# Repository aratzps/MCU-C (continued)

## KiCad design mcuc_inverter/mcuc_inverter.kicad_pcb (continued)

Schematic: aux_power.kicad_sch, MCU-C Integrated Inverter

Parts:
C601, C602: 0.68uF 630VDC X2 film; C_Rect_L26.5mm_W10.5mm_P22.50mm_MKS4; Rating Radial box 26.5 x 16.5 x 10.5 mm, 22.5 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
C603: 6.8nF 630V C0G; C_1210_3225Metric; Rating TDK CGA5H4C0G2J682J115AE (DER-948Q clam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
C604, C640, C645: 10uF 50V X7R; C_1210_3225Metric
C606: 0.47uF 50V X7R; C_0805_2012Metric; Rating BPP: 0.47uF selects STANDARD ILIMIT (CR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
C607: 100nF 50V X7R; C_0805_2012Metric
C608: 1nF 200V C0G; C_0805_2012Metric
C609, C610: 220uF 25V polymer [TBV]; CP_Elec_8x10.5
C611, C622, C623, C642, C646, C661, C663, C665, C667, C669, C671, C673, C675, C677, C679, C681, C683: 100nF; C_0603_1608Metric
C612: 270pF; C_0603_1608Metric
C613, C625: 10nF [TBV]; C_0603_1608Metric
C614: 2.2uF 25V X7R; C_0805_2012Metric; Rating BPS: 0805 min per datasheet (>=1.5uF in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
C620, C621: 4.7uF 50V [TBV]; C_0805_2012Metric
C624: 4.7uF [TBV]; C_0603_1608Metric
C626: 100pF [TBV]; C_0603_1608Metric
C627: 47nF [TBV]; C_0603_1608Metric
C628: 130pF; C_0603_1608Metric
C629, C630, C643, C644, C647, C648: 22uF 25V [TBV]; C_1210_3225Metric
C631: 1uF [TBV]; C_0603_1608Metric
C641, C649: 220nF 50V X7R; C_0603_1608Metric
C650, C651, C653, C660, C666, C672, C678: 10uF [TBV]; C_0805_2012Metric
C652: 2.2uF [TBV]; C_0603_1608Metric
C654, C655: 1uF 16V X7R; C_0603_1608Metric
C662, C664, C668, C670, C674, C676, C680, C682: 10uF 25V [TBV]; C_0805_2012Metric
C684, C685, C686, C687: 10uF 25V X7R; C_0805_2012Metric
D601: US1M-class 1kV std recovery [TBV]; D_SMA
D602: BAS316-class [TBV]; D_SOD-323
D603: SS310-class 100V 3A [TBV]; D_SMC
D604: SS54 [TBV]; D_SMC
D605, D606, D608, D609, D611, D612, D614, D615: SS310 [TBV]; D_SMC
D607, D610, D613, D616: MM3Z4V7ST1G 4.7V; D_SOD-323
D620: BZX384-C9V1 [TBV]; D_SOD-323
D621, D622, D623, D624: MMSZ5245C-E3-08 15V 2%; D_SOD-123
D625, D626, D627, D628: 1N4148W-7-F; D_SOD-123
D629: SMCJ36CA; D_SMC
D630: MMSZ5243BT1G 13V; D_SOD-123
L601, L602: SRP6060FA-100M 10uH 7.6A; L_Bourns_SRP6060FA
L603: SRR1260-120M 12uH 5A; L_Bourns_SRR1260
Q601, Q602, Q603, Q604, Q605: CSD18543Q3A-class [TBV]; VSON-8_3.3x3.3mm_P0.65mm_NexFET
Q606, Q607, Q608, Q609: BCP56-16T1G; SOT-223-3_TabPin2
Q610: DMP6023LE-13; SOT-223-3_TabPin2
R603, R604, R612, R613, R614, R615: 39k; R_1206_3216Metric; Rating 0.5W 200V working (ROHM ESR18EZPJ393); Tolerance 5%
R605: 4.7R; R_1206_3216Metric; Rating 0.5W 200V working (ROHM ESR18EZPJ4R7)
R606: 8.2k [TBV]; R_0603_1608Metric
R607: 100R [TBV]; R_0603_1608Metric
R608: 10R; R_1206_3216Metric; Rating 0.5W 200V working (ROHM ESR18EZPJ100); 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
R609: 143k 1%; R_0603_1608Metric
R610: 13.2k 1%; R_0603_1608Metric
R611: 10k [TBV]; R_0603_1608Metric
R616, R617, R618, R619: 300k; R_1206_3216Metric; Tolerance 1%; Rating 0.5W 200V working (ROHM ESR18 class)
R620: 100k [TBV]; R_0603_1608Metric
R621: 16.2k [TBV]; R_0603_1608Metric
R622: 30mR 1%; R_2512_6332Metric
R623: 97.6k 1%; R_0603_1608Metric
R624: 4.99k 1%; R_0603_1608Metric
R625: 24.9k [TBV]; R_0603_1608Metric
R626: 84.5k (300kHz) [TBV]; R_0603_1608Metric
R627: 93.1k (CCM+hiccup) [TBV]; R_0603_1608Metric
R630: 210k; R_0603_1608Metric; Tolerance 1%; Rating 0.5W 200V working (ROHM ESR18EZPJ4R7)
R640, R642: 100k 1%; R_0603_1608Metric
R641: 24.9k 1%; R_0603_1608Metric
R643: 9.09k 1%; R_0603_1608Metric
R644, R645, R646, R647: 470R 1%; R_0603_1608Metric
R648: 100k; R_0603_1608Metric
T601: custom flyback per DER-948Q T1: Lp 422.6uH, 25T:2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; T_FLYBACK_EQ30
T602, T603, T604, T605: 750316856; WE_PPTI_750316856
U601: INN3990CQ; InSOP-24D
U603: LM5175RHFR; VQFN-28-1EP_4x5mm_P0.5mm_EP2.55x3.55mm
U604: LM74610QDGKRQ1; VSSOP-8_3x3mm_P0.65mm
U605, U606: LMR33630ADDAR; SOIC-8-1EP_3.9x4.9mm_P1.27mm_EP2.95x4.9mm_Mask2.71x3.4mm
U607: TLV1117-33; SOT-223-3_TabPin2
U608: NXE2S0505MC; Converter_DCDC_Murata_NXExSxxxxMC_SMD
U609, U610, U611, U612: SN6505BDBVR; SOT-23-6

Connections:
+5V: C643.1, C644.1, C650.1, C652.1, C660.1, C661.1, C666.1, C667.1, C672.1, C673.1, C678.1, C679.1, L602.2, R640.1, T602.2 (CT_PRI), T603.2 (CT_PRI), T604.2 (CT_PRI), T605.2 (CT_PRI), U607.3 (VI), U608.3 (+VIN), U609.2 (VCC), U609.5 (EN), U610.2 (VCC), U610.5 (EN), U611.2 (VCC), U611.5 (EN), U612.2 (VCC), U612.5 (EN); also elsewhere on the board
+12V: C647.1, C648.1, L603.2, R642.1; also elsewhere on the board
/AUX_IN: D629.1 (A1), Q610.2 (D); also elsewhere on the board
/Auxiliary power/AUX_15V: C640.1, C641.1, C645.1, C649.1, D604.1 (K), Q605.5 (D), U604.8 (CATHODE), U605.2 (VIN), U605.3 (EN), U606.2 (VIN), U606.3 (EN)
/Auxiliary power/AUX_IN_P: C620.1, C621.1, D630.1 (K), Q601.5 (D), Q610.3 (S), R620.1, U603.27 (VIN), U603.28 (VISNS)
/Auxiliary power/BB_15V: C629.1, C630.1, Q604.5 (D), Q605.1 (S), Q605.2 (S), Q605.3 (S), R623.1, U603.9 (VOSNS), U603.10 (ISNS(-)), U603.11 (ISNS(+)), U603.21 (BIAS), U604.4 (ANODE)
/Auxiliary power/BB_COMP: C626.1, R625.1, U603.6 (COMP)
/Auxiliary power/BB_CS: Q602.1 (S), Q602.2 (S), Q602.3 (S), Q603.1 (S), Q603.2 (S), Q603.3 (S), R622.1, U603.13 (CS)
/Auxiliary power/BB_FB: R623.2, R624.1, U603.8 (FB)
/Auxiliary power/BB_MODE: R627.1, U603.1 (MODE)
/Auxiliary power/BB_RT: R626.1, U603.3 (RT/SYNC)
/Auxiliary power/BB_SLOPE: C628.1, U603.4 (SLOPE)
/Auxiliary power/BB_SS: C627.1, U603.5 (SS)
/Auxiliary power/BB_SW1: C622.2, L601.1, Q601.1 (S), Q601.2 (S), Q601.3 (S), Q602.5 (D), U603.25 (SW1)
/Auxiliary power/BB_SW2: C623.2, L601.2, Q603.5 (D), Q604.1 (S), Q604.2 (S), Q604.3 (S), U603.15 (SW2)
/Auxiliary power/BB_VCC: C624.1, U603.20 (VCC)
/Auxiliary power/CLAMP_NODE: C603.2, R605.1, R614.2, R615.2
/Auxiliary power/DC_BUS_P: C601.1, C603.1, R603.1, R604.1, R616.1, T601.3 (PRI+); also elsewhere on the board
/Auxiliary power/FB_5V: R640.2, R641.1, U605.5 (FB)
/Auxiliary power/FB_12V: R642.2, R643.1, U606.5 (FB)
/Auxiliary power/FLY_15V: C608.2, C609.1, C610.1, C611.1, D603.1 (K), D604.2 (A), R609.1, R611.1, U601.6 (VOUT)
/Auxiliary power/VGD_HS1_RAW: C662.1, C663.1, D605.1 (K), D606.1 (K), Q606.2 (C), R644.1
/Auxiliary power/VGD_HS2_RAW: C668.1, C669.1, D608.1 (K), D609.1 (K), Q607.2 (C), R645.1
/Auxiliary power/VGD_HS3_RAW: C674.1, C675.1, D611.1 (K), D612.1 (K), Q608.2 (C), R646.1
/Auxiliary power/VGD_LS_RAW: C680.1, C681.1, D614.1 (K), D615.1 (K), Q609.2 (C), R647.1
/Auxiliary power/V_SENSE: R630.1, U601.13 (V)
/Precharge and contactor/DC_BUS_N: C602.2, C604.2, C606.2, C607.2, D620.2 (A), T601.5 (BIAS-), U601.16 (S), U601.17 (S), U601.18 (S), U601.19 (S); also elsewhere on the board
/VGD_HS1_COM: C662.2, C663.2, C664.1, C665.1, C684.2, D607.1 (K), D621.2 (A); also elsewhere on the board
/VGD_HS1_N: C664.2, C665.2, D607.2 (A), T602.5 (CT_SEC); also elsewhere on the board
/VGD_HS1_P: C684.1, Q606.3 (E); also elsewhere on the board
/VGD_HS2_COM: C668.2, C669.2, C670.1, C671.1, C685.2, D610.1 (K), D622.2 (A); also elsewhere on the board
/VGD_HS2_N: C670.2, C671.2, D610.2 (A), T603.5 (CT_SEC); also elsewhere on the board
/VGD_HS2_P: C685.1, Q607.3 (E); also elsewhere on the board
/VGD_HS3_COM: C674.2, C675.2, C676.1, C677.1, C686.2, D613.1 (K), D623.2 (A); also elsewhere on the board
/VGD_HS3_N: C676.2, C677.2, D613.2 (A), T604.5 (CT_SEC); also elsewhere on the board
/VGD_HS3_P: C686.1, Q608.3 (E); also elsewhere on the board
/VGD_LS_COM: C680.2, C681.2, C682.1, C683.1, C687.2, D616.1 (K), D624.2 (A); also elsewhere on the board
/VGD_LS_N: C682.2, C683.2, D616.2 (A), T605.5 (CT_SEC); also elsewhere on the board
/VGD_LS_P: C687.1, Q609.3 (E); also elsewhere on the board
GND: C609.2, C610.2, C611.2, C612.2, C614.2, C620.2, C621.2, C624.2, C625.2, C626.2, C627.2, C628.2, C629.2, C630.2, C640.2, C641.2, C643.2, C644.2, C645.2, C647.2, C648.2, C649.2, C650.2, C651.2, C652.2, C654.2, C655.2, C660.2, C661.2, C666.2, C667.2, C672.2, C673.2, C678.2, C679.2, D629.2 (A2), R610.2, R621.2, R622.2, R624.2, R626.2, R627.2, R641.2, R643.2, R648.2, T601.9 (SEC-), U601.1 (IS), U601.2 (GND), U601.5 (SR), U603.2 (DITH), U603.7 (AGND), U603.12 (CSG), U603.19 (PGND), U603.29 (PowerPAD), U605.1 (PGND), U605.9 (AGND), U606.1 (PGND), U606.9 (AGND), U607.1 (GND), U608.1 (-VIN), U609.4 (GND), U609.6 (CLK), U610.4 (GND), U610.6 (CLK), U611.4 (GND), U611.6 (CLK), U612.4 (GND), U612.6 (CLK); also elsewhere on the board
unnamed: C601.2, C602.1
unnamed: C608.1, R608.2
unnamed: C613.1, R611.2
unnamed: C625.1, R625.2
unnamed: D601.2 (A), T601.1 (PRI-), U601.24 (D)
unnamed: D601.1 (K), R605.2
unnamed: D602.2 (A), T601.6 (BIAS+)
unnamed: C604.1, D602.1 (K), R606.1
unnamed: D603.2 (A), R607.1, R608.1, T601.8 (SEC+)
unnamed: D605.2 (A), T602.6 (N3.A)
unnamed: D606.2 (A), T602.4 (N4.B)
unnamed: D608.2 (A), T603.6 (N3.A)
unnamed: D609.2 (A), T603.4 (N4.B)
unnamed: D611.2 (A), T604.6 (N3.A)
unnamed: D612.2 (A), T604.4 (N4.B)
unnamed: D614.2 (A), T605.6 (N3.A)
unnamed: D615.2 (A), T605.4 (N4.B)
unnamed: D620.1 (K), R619.2, R630.2
unnamed: D621.1 (K), D625.1 (K)
unnamed: D622.1 (K), D626.1 (K)
unnamed: D623.1 (K), D627.1 (K)
unnamed: D624.1 (K), D628.1 (K)
unnamed: D625.2 (A), Q606.1 (B), R644.2
unnamed: D626.2 (A), Q607.1 (B), R645.2
unnamed: D627.2 (A), Q608.1 (B), R646.2
unnamed: D628.2 (A), Q609.1 (B), R647.2
unnamed: D630.2 (A), Q610.1 (G), R648.1
unnamed: Q601.4 (G), U603.24 (HDRV1)
unnamed: Q602.4 (G), U603.22 (LDRV1)
unnamed: Q603.4 (G), U603.18 (LDRV2)
unnamed: Q604.4 (G), U603.16 (HDRV2)
unnamed: Q605.4 (G), U604.2 (GATE_PD), U604.6 (GATE_DRV)
unnamed: R603.2, R604.2, R612.1, R613.1
unnamed: R612.2, R613.2, R614.1, R615.1
unnamed: R616.2, R617.1
unnamed: R617.2, R618.1
unnamed: R618.2, R619.1
unnamed: T602.1 (N1.A), U609.1 (D1)
unnamed: T602.3 (N2.B), U609.3 (D2)
unnamed: T603.1 (N1.A), U610.1 (D1)
unnamed: T603.3 (N2.B), U610.3 (D2)
unnamed: T604.1 (N1.A), U611.1 (D1)
unnamed: T604.3 (N2.B), U611.3 (D2)
unnamed: T605.1 (N1.A), U612.1 (D1)
unnamed: T605.3 (N2.B), U612.3 (D2)
unnamed: C606.1, C607.1, R606.2, U601.14 (BPP)
unnamed: C614.1, U601.4 (BPS)
unnamed: C612.1, C613.2, R609.2, R610.1, U601.3 (FB)
unnamed: R607.2, U601.7 (FWD)
unnamed: C622.1, U603.23 (BOOT1)
unnamed: C623.1, U603.17 (BOOT2)
unnamed: R620.2, R621.1, U603.26 (EN/UVLO)
unnamed: C631.1, U604.7 (VCAPH)
unnamed: C631.2, U604.1 (VCAPL)
unnamed: C642.1, U605.7 (BOOT)
unnamed: C642.2, L602.1, U605.8 (SW)
unnamed: C654.1, U605.6 (VCC)
unnamed: C646.1, U606.7 (BOOT)
unnamed: C646.2, L603.1, U606.8 (SW)
unnamed: C655.1, U606.6 (VCC)

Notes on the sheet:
Auxiliary power
SPEC.md 11.2b - DECISIONS.md D020. HV flyback (INN3990CQ) -> 15 V main rail; LM5175 buck-boost from 12-24 V AUX_IN OR'd in via LM74610 smart diode; LMR51430 bucks -> 5 V / 12 V; TLV1117 -> 3.3 V; 4x SN6505B+750316856 gate supplies; NXE2S0505MC CAN 5 V.
ISOLATION: primary side of T601 floats at HV bus potential (48-450 V, 500 V transient). Spacing per SPEC 10: >=3.2 mm clearance / >=6.4 mm creepage power->control, T601 reinforced >=4 kV. FluxLink feedback is internal to U601 (no optocoupler). Film caps C601/C602 in series so no single part spans t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
SR pin tied to GND: diode-only rectification (datasheet: 'If no SR FET is used connect this pin to GND'). IS tied to GND: no CC regulation. FB divider 143k/13.2k @ 1.265 V ref -> 14.97 V. Feed-forward 10k + 10 nF per Fig 10.
D604 SS54: plain Schottky OR from flyback into AUX_15V. Penalty ~0.4 V / ~0.7 W at 1.7 A. Upgrade: second LM74610+FET stage [TBV]. Flyback is the primary source; the LM5175 aux path carries the board only when the 12-24 V feed is present (15.02 V > 14.97 - 0.4 V).
Primary OVP chain (not fitted - note per datasheet): zener + series R + blocking diode from the rectified bias rail into BPP triggers latching OVP at ISD. Fit if secondary OVP insufficient [TBV].
AUX input: LM5175 4-switch buck-boost, 12-24 V in -> 15.02 V (FB 88.7k/4.99k @ 0.8 V). fsw 300 kHz (RT 84.5k), CCM+hiccup (MODE 93.1k), all loop/support values [TBV]. EN divider 100k/16.2k -> input UVLO ~8.9 V [TBV]. ISNS+/- shorted (CC loop disabled).
Gate-drive supplies (x4): SN6505B push-pull from +5V (SN6505B is 5 V-only, D020) + WE 750316856 (1:4.67 CT:CT) -> 22-25 V raw full-wave rail (VGD_x_RAW). MM3Z4V7ST1G zener from raw(-) sets COM 4.7 V above it, so COM-N = -4.7 V; the +15 V leg is then POST-REGULATED per D026 (see the note at the left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
+5V / +12V / +3.3V / GND are global power rails sourced on this sheet (PWR_FLAG on +5V here; +12V flagged on precharge sheet, +3.3V and GND flagged on MCU sheet - no duplicates).
CAN supply: functional 3 kVDC isolation. CAN_GND is the isolated CAN return - do not tie to GND.
RAW
COM-4.7 V
MJ-14 FIXED - line UV sense fitted (clamped network, InnoSwitch3-AQ datasheet Fig. 15). R616-R619 4x 300k (RU = 1.20 M) + R630 210k (RL) + D620 9.1 V zener at the RL top node. Brown-in V_UV+ = I_UV+ x (RU+RL) + 1.37 V; I_UV+ 22.1/26.1/30.4 uA over temp -> 32.5 / 38.2 / 44.2 V. Max 44.2 V < the 48 V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
CR-4 FIXED - RCD clamp respec. R603/R604/R612-R615 = 6x 39k 1206 (0.5 W, 200 V working, ROHM ESR18 class) wired 3 series x 2 parallel = 58.5 k. Old build was 2x 390k 0603 in parallel (195 k) on parts rated 75 V / 0.1 W - 3-5x over voltage and over power. V_OR = 15.5 V x 12.5 = 194 V. P_leak = 0.5 x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
CR-5 FIXED - core saturation at the current limit. C606 (BPP) 4.7 uF -> 0.47 uF, which selects the STANDARD I_LIMIT instead of I_LIMIT+1. Controller stays INN3990CQ. B_pk = Lp x I_LIM / (Np x Ae) = 422.6 uH x I / (25 x 108 mm^2) = 0.1565 T/A: was 4.7 uF -> I_LIMIT+1 2.576 A typ / 2.886 A worst -> 4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
MJ-19 - aux input priority (D020) now actually implemented by setpoint offset: flyback 14.97 V (R609/R610 143k/13.2k @ 1.265 V) vs LM5175 16.45 V (R623 88.7k -> 97.6k). Worst case: LM5175 min 16.45 x 0.975 = 16.04 V > flyback max 14.97 x 1.03 = 15.42 V, margin 0.62 V - the aux unit always holds the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
INSULATION CAVEAT (D017) - the four gate-drive transformers T602-T605 (WE 750316856) carry SUPPLEMENTARY / FUNCTIONAL insulation only, 600 Vrms working; their 2.5 kV AC figure is a type-test hipot, not a reinforced certification. The REINFORCED barrier on the gate-drive path therefore rests ENTIREL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
HS1 +15 V post-regulator (D026)
HS2 +15 V post-regulator (D026)
HS3 +15 V post-regulator (D026)
LS +15 V post-regulator (D026)
D026 - +15 V GATE RAIL POST-REGULATION. REQUIRED: the raw rail alone breaks the module AMR. Raw secondary = 5 V +-2.5% x 4.67 = 22.77-23.93 V per half, less the SS310 Vf; at light load the leakage peak-charges the reservoir to ~24.9 V. Minus the COM zener that is V_GS(on) = 20.3 V against the FS02M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
MN-14 FIXED - AUX INPUT PROTECTION (12-24 V feed, J1203 on the comms sheet). Previously a reversed connection ran straight through the LM5175 body diodes with nothing in the way. D629 SMCJ36CA - BIDIRECTIONAL TVS, DO-214AB. Littelfuse SMCJ datasheet: V_RWM 36 V, V_C 58.1 V at rated I_PP at I_T 1 mA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

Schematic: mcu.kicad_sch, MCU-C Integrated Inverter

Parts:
C1, C2, C3, C4, C5, C6, C9, C12: 100nF; C_0603_1608Metric
C7: 4.7uF; C_0805_2012Metric
C8: 1uF; C_0603_1608Metric
C10, C11: 2.2uF; C_0805_2012Metric
C13, C14: 18pF; C_0603_1608Metric
FB1: FerriteBead; L_0805_2012Metric
R1: 10k; R_0603_1608Metric
U1: STM32F405VGT6; LQFP-100_14x14mm_P0.5mm
Y1: 8MHz; Crystal_SMD_5032-2Pin_5.0x3.2mm

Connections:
/CAN1_RX: U1.95 (PB8); also elsewhere on the board
/CAN1_TX: U1.96 (PB9); also elsewhere on the board
/CONTACTOR_EN: U1.2 (PE3); also elsewhere on the board
/DISCHARGE_EN: U1.3 (PE4); also elsewhere on the board
/DRV_RST_IN: U1.86 (PD5); also elsewhere on the board
/ENC_A: U1.63 (PC6); also elsewhere on the board
/ENC_B: U1.64 (PC7); also elsewhere on the board
/ENC_I: U1.65 (PC8); also elsewhere on the board
/FAULT_RESET: U1.85 (PD4); also elsewhere on the board
/HALL_1: U1.59 (PD12); also elsewhere on the board
/HALL_2: U1.60 (PD13); also elsewhere on the board
/HALL_3: U1.61 (PD14); also elsewhere on the board
/I_PH_1: U1.15 (PC0); also elsewhere on the board
/I_PH_2: U1.16 (PC1); also elsewhere on the board
/I_PH_3: U1.17 (PC2); also elsewhere on the board
/I_REF_1: U1.29 (PA4); also elsewhere on the board
/I_REF_2: U1.32 (PA7); also elsewhere on the board
/I_REF_3: U1.36 (PB1); also elsewhere on the board
/LED_FAULT: U1.97 (PE0); also elsewhere on the board
/MCU/3V3A: C8.1, C9.1, FB1.2, U1.21 (VREF+), U1.22 (VDDA)
/MCU/PWM_HS_1: U1.67 (PA8); also elsewhere on the board
/MCU/PWM_HS_2: U1.68 (PA9); also elsewhere on the board
/MCU/PWM_HS_3: U1.69 (PA10); also elsewhere on the board
/MCU/PWM_LS_1: U1.52 (PB13); also elsewhere on the board
/MCU/PWM_LS_2: U1.53 (PB14); also elsewhere on the board
/MCU/PWM_LS_3: U1.54 (PB15); also elsewhere on the board
/MOTOR_TEMP: U1.33 (PC4); also elsewhere on the board
/NRST: C12.1, U1.14 (NRST); also elsewhere on the board
/OC_LATCHED: U1.84 (PD3); also elsewhere on the board
/PPM: U1.92 (PB6); also elsewhere on the board
/PRECHARGE_EN: U1.1 (PE2); also elsewhere on the board
/RES_NFAULT: U1.83 (PD2); also elsewhere on the board
/RES_SPI_MISO: U1.79 (PC11); also elsewhere on the board
/RES_SPI_NCS: U1.77 (PA15); also elsewhere on the board
/RES_SPI_NRDVEL: U1.82 (PD1); also elsewhere on the board
/RES_SPI_NSAMPLE: U1.81 (PD0); also elsewhere on the board
/RES_SPI_SCK: U1.78 (PC10); also elsewhere on the board
/SINCOS_COS: U1.31 (PA6); also elsewhere on the board
/SINCOS_SIN: U1.30 (PA5); also elsewhere on the board
/SWCLK: U1.76 (PA14); also elsewhere on the board
/SWDIO: U1.72 (PA13); also elsewhere on the board
/Supervisor and interlocks/FAULT_BKIN: U1.51 (PB12); also elsewhere on the board
/TEMP_BOARD: U1.35 (PB0); also elsewhere on the board
/TEMP_COLDPLATE: U1.26 (PA3); also elsewhere on the board
/USB_DM: U1.70 (PA11); also elsewhere on the board
/USB_DP: U1.71 (PA12); also elsewhere on the board
/USB_VBUS_SENSE: U1.34 (PC5); also elsewhere on the board
/V_BUS: U1.18 (PC3); also elsewhere on the board
GND: C1.2, C2.2, C3.2, C4.2, C5.2, C6.2, C7.2, C8.2, C9.2, C10.2, C11.2, C12.2, C13.1, C14.1, R1.2, U1.10 (VSS), U1.20 (VSSA), U1.27 (VSS), U1.74 (VSS), U1.99 (VSS); also elsewhere on the board
unnamed: R1.1, U1.94 (BOOT0)
unnamed: C13.2, U1.12 (PH0), Y1.2
unnamed: C14.2, U1.13 (PH1), Y1.1
unnamed: C10.1, U1.49 (VCAP_1)
unnamed: C11.1, U1.73 (VCAP_2)

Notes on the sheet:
MCU
STM32F405VGT6 core: power/decoupling, VDDA filter, VCAP, BOOT0, NRST, 8 MHz HSE, SWD, TIM1 PWM + BKIN, CAN1, USB. SPEC.md 12
Decoupling: one 100nF per VDD pin + 4.7uF bulk (+3.3V rail generated in Auxiliary power sheet)
VDDA / VREF+ supply filter
PA0 / PA1 / PA2 (pins 23/24/25): reserved SENS1/2/3 phase-voltage inputs, not fitted (DECISIONS.md D023)
PB10 / PB11 (pins 47/48): reserved UART3 / I2C2 expansion (D023)

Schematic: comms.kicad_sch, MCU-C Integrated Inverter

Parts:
C1201, C1202: 100nF; C_0603_1608Metric
C1203: 4.7nF; C_0603_1608Metric
C1204, C1205: 4.7uF; C_0805_2012Metric
D1201: NUP2105L; SOT-23
D1202: GREEN PWR; LED_0805_2012Metric
D1203: RED FAULT; LED_0805_2012Metric
J1201: CAN bus (H/L/GND/nc); JST_PH_B4B-PH-K_1x04_P2.00mm_Vertical
J1202: GCT USB4085-GF-A; USB_C_Receptacle_GCT_USB4085
J1203: Aux 12-24 V in; JST_VH_B2P-VH_1x02_P3.96mm_Vertical
J1204: Main contactor coil; JST_VH_B4P-VH_1x04_P3.96mm_Vertical
J1205: Hall + motor temp; JST_SH_SM08B-SRSS-TB_1x08-1MP_P1.00mm_Horizontal
J1206: Encoder / SinCos; JST_SH_SM08B-SRSS-TB_1x08-1MP_P1.00mm_Horizontal
J1207: Resolver; JST_SH_SM06B-SRSS-TB_1x06-1MP_P1.00mm_Horizontal
J1208: FTSH-105-01-L-DV-K; PinHeader_2x05_P1.27mm_Vertical_SMD
JP1201: TERM_H; SolderJumper-2_P1.3mm_Bridged_RoundedPad1.0x1.5mm
JP1202: TERM_L; SolderJumper-2_P1.3mm_Bridged_RoundedPad1.0x1.5mm
R1202, R1203: 60.4R; R_0603_1608Metric
R1204, R1205: 5.1k; R_0603_1608Metric
R1206: 47k; R_0603_1608Metric
R1207: 22k; R_0603_1608Metric
R1208, R1209: 1k; R_0603_1608Metric
U1201: ISO1042DWR; SOIC-16W_7.5x10.3mm_P1.27mm
U1202: USBLC6-2SC6; SOT-23-6

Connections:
+12V: J1204.1; also elsewhere on the board
/AUX_IN: J1203.1; also elsewhere on the board
/CAN1_RX: U1201.5 (RXD); also elsewhere on the board
/CAN1_TX: U1201.3 (TXD); also elsewhere on the board
/CONTACTOR_N: J1204.2; also elsewhere on the board
/Communications/CANH: D1201.1 (K), J1201.1, JP1201.1 (A), U1201.13 (CANH)
/Communications/CANL: D1201.2 (K), J1201.2, JP1202.1 (A), U1201.12 (CANL)
/Communications/ENC_A_IN: J1206.2; also elsewhere on the board
/Communications/ENC_B_IN: J1206.3; also elsewhere on the board
/Communications/ENC_I_IN: J1206.4; also elsewhere on the board
/Communications/HALL_1_IN: J1205.2; also elsewhere on the board
/Communications/HALL_2_IN: J1205.3; also elsewhere on the board
/Communications/HALL_3_IN: J1205.4; also elsewhere on the board
/Communications/RES_COS_N: J1207.6; also elsewhere on the board
/Communications/RES_COS_P: J1207.5; also elsewhere on the board
/Communications/RES_EXC_N: J1207.2; also elsewhere on the board
/Communications/RES_EXC_P: J1207.1; also elsewhere on the board
/Communications/RES_SIN_N: J1207.4; also elsewhere on the board
/Communications/RES_SIN_P: J1207.3; also elsewhere on the board
/Communications/SINCOS_COS_IN: J1206.6; also elsewhere on the board
/Communications/SINCOS_SIN_IN: J1206.5; also elsewhere on the board
/Communications/USB_CC1: J1202.A5 (CC1), R1204.1
/Communications/USB_CC2: J1202.B5 (CC2), R1205.1
/Communications/VBUS_DET: J1202.A4 (VBUS), J1202.A9 (VBUS), J1202.B4 (VBUS), J1202.B9 (VBUS), R1206.1, U1202.5 (VBUS)
/LED_FAULT: D1203.1 (K); also elsewhere on the board
/MOTOR_TEMP: J1205.5; also elsewhere on the board
/NRST: J1208.10 (~RESET); also elsewhere on the board
/PPM: J1206.7; also elsewhere on the board
/SWCLK: J1208.4 (SWCLK/TCK); also elsewhere on the board
/SWDIO: J1208.2 (SWDIO/TMS); also elsewhere on the board
/USB_DM: U1202.6 (I/O1); also elsewhere on the board
/USB_DP: U1202.4 (I/O2); also elsewhere on the board
/USB_VBUS_SENSE: R1206.2, R1207.1; also elsewhere on the board
GND: C1201.2, C1205.2, D1202.1 (K), J1202.A1 (GND), J1202.A12 (GND), J1202.B1 (GND), J1202.B12 (GND), J1202.S1 (SHIELD), J1203.2, J1204.3, J1205.6, J1205.7, J1205.8, J1206.8, J1208.3 (GND), J1208.5 (GND), J1208.9 (GNDDetect), R1204.2, R1205.2, R1207.2, U1201.2 (GND1), U1201.8 (GND1), U1202.2 (GND); also elsewhere on the board
unnamed: C1203.1, R1202.2, R1203.1
unnamed: D1202.2 (A), R1208.2
unnamed: D1203.2 (A), R1209.2
unnamed: J1202.A6 (D+), J1202.B6 (D+), U1202.3 (I/O2)
unnamed: J1202.A7 (D-), J1202.B7 (D-), U1202.1 (I/O1)
unnamed: JP1201.2 (B), R1202.1
unnamed: JP1202.2 (B), R1203.2

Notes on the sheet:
Communications and connectors
SPEC.md 12/13, DECISIONS.md D020/D022. Isolated CAN (ISO1042DWR), USB-C 2.0 FS device, SWD debug, status LEDs, board connector bank. CAN topology ported from PALTA pcb_design/CAN.sch (ISO1050 -> ISO1042, D022).
ISOLATED CAN: CAN_5V/CAN_GND come from the aux sheet's NXE2S0505MC (3 kVDC, functional isolation; reinforced barrier budget sits in the HV-facing devices). Legacy CAN.sch reverse-polarity FET (2N7002+MBR0540 on the external 5 V feed) dropped - supply is on-board now. TVS added: legacy sheet's own n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
C1201 100 nF + C1205 4.7 uF at U1201 pin 1 (VCC1). TI SLLSF09E section 10 requires a 0.1 uF AND a >= 4.7 uF bulk capacitor on BOTH supply pins. VCC2 already had C1202 100 nF + C1204 4.7 uF; VCC1 had only the 100 nF (review 3 minor).
Split termination (PALTA pattern): 2 x 60.4R + 4.7 nF to CAN_GND = 120R differential. END-NODE ONLY - and now SELECTABLE (review 3 minor): JP1201/JP1202 are solder jumpers in series with R1202/R1203, shipped BRIDGED so the board leaves fabrication terminated. Cut BOTH bridges to run the inverter mi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
Dual-line CAN TVS, 24 V working (NUP2105L-class [TBV], SZNUP2105LT1G).
USB 2.0 FS device (VESC tool). USB is user-accessible: the reinforced barrier is UPSTREAM - the whole control domain is separated from HV by the gate-driver / AMC1311 / HOYS / ISO1042 barriers (SPEC 5, D017/D022) - so no extra isolation here. USBLC6-2SC6 pinout (SOT-23-6): 1 I/O1, 2 GND, 3 I/O2, 4 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
5.1k CC pulldowns = UFP (device) role.
SHIELD tied to GND at the receptacle (chassis strategy at layout).
SWD debug: Samtec FTSH-105-01-L-DV-K, 10-pin 1.27 mm, standard ARM Cortex debug pinout (SWO/TDI unused).
Status LEDs: green PWR direct from +3.3 V; red FAULT is LOW-SIDE driven - LED_FAULT pulled low lights it (driver assignment on the supervisor/MCU pass).
BOARD CONNECTOR BANK - generic header symbols; final connector P/Ns in the BOM (JST families as placeholders).
CONTACTOR_P/N: coil pair driven on the precharge sheet (+12 V feed, low-side switch + flyback there). Pin 4 spare. Precharge relay K401 is ON-BOARD (precharge sheet) - its coil needs no connector.
Halls are open-collector with 3.3 V pull-ups on the position sheet (PALTA precedent) - connector supplies +3.3 V + GND.
PHASE-CURRENT SENSORS: the three HOYS 200-S/SP33 are chassis-mounted on the phase busbars (apertures) and arrive on 5-pin JST PA harnesses (B05B-PASK class). Their transducer symbols live on the current_sense sheet; board-side harness connectors are footprints on those same nets, handled at layout 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
J1206 pin 7: PPM (servo) input to MCU PB6/TIM4_CH1 - was the spare position (previously tied to GND).

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
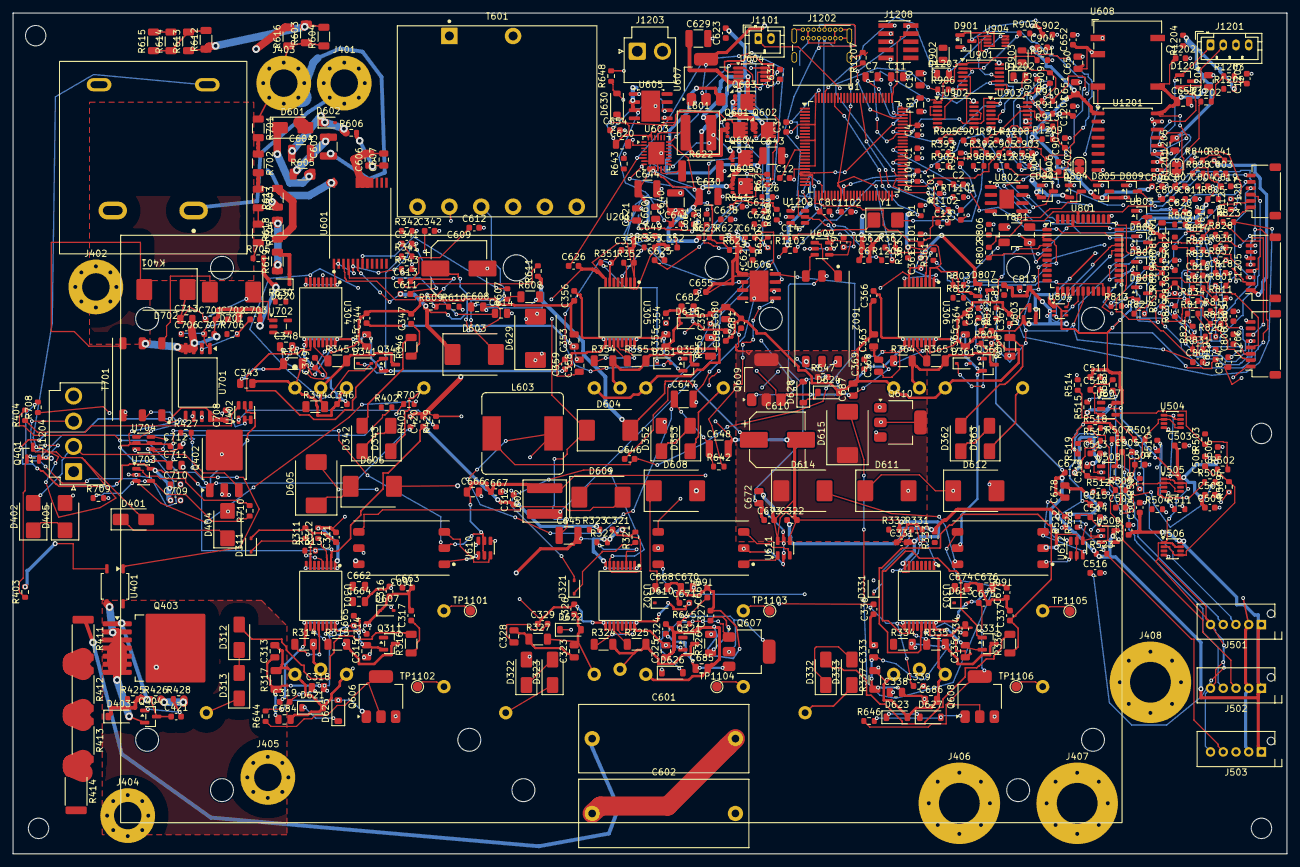
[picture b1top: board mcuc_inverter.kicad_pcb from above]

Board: 4 copper layers, 200.0 x 132.0 mm, 564 parts (0 on the bottom side), 347 nets.

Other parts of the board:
C510, C512, C514, C516: 1nF; C_0603_1608Metric
C511, C513, C515: 100nF; C_0603_1608Metric
J406: PHASE_U motor output stud - M6 ring lug [TBV]; MountingHole_6.4mm_M6_Pad_Via
J407: PHASE_V motor output stud - M6 ring lug [TBV]; MountingHole_6.4mm_M6_Pad_Via
J408: PHASE_W motor output stud - M6 ring lug [TBV]; MountingHole_6.4mm_M6_Pad_Via
MH1, MH2, MH3, MH4: MountingHole_3.2mm_M3
R513, R517, R521: 100R; R_0603_1608Metric
R514, R518, R522: 100k; R_0603_1608Metric
R515, R519, R523: 1M; R_0603_1608Metric
U507, U508, U509: OPA376AIDBVR; SOT-23-5

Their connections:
/I_REF_1: C510.1, R513.2, U507.3; also elsewhere on the board
/I_REF_2: C512.1, R517.2, U508.3; also elsewhere on the board
/I_REF_3: C514.1, R521.2, U509.3; also elsewhere on the board
/Phase current sensing/HOYS_U_OUT: R514.1; also elsewhere on the board
/Phase current sensing/HOYS_U_REF: R513.1, R515.2; also elsewhere on the board
/Phase current sensing/HOYS_V_OUT: R518.1; also elsewhere on the board
/Phase current sensing/HOYS_V_REF: R517.1, R519.2; also elsewhere on the board
/Phase current sensing/HOYS_W_OUT: R522.1; also elsewhere on the board
/Phase current sensing/HOYS_W_REF: R521.1, R523.2; also elsewhere on the board
/Phase current sensing/OC_TRIP: C516.1; also elsewhere on the board
GND: C510.2, C511.2, C512.2, C513.2, C514.2, C515.2, C516.2, R514.2, R518.2, R522.2, U507.2, U508.2, U509.2; also elsewhere on the board

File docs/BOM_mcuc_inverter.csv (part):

"Reference","Value","Footprint","QUANTITY","DNP","EXCLUDE_FROM_BOARD"
"C1-C6,C9,C12,C501,C503,C504,C506,C507,C509,C611,C622,C623,C642,C646,C661,C663,C665,C667,C669,C671,C673,C675,C677,C679,C681,C683,C703,C706,C708,C710,C801,C802,C804,C806,C807,C813,C815,C816,C818,C901-C904,C1101,C1102,C1201,C1202","100nF","Capacitor_SMD:C_0603_1608Metric","52","",""
"C7,C1204","4.7uF","Capacitor_SMD:C_0805_2012Metric","2","",""
"C8,C701,C702,C707,C709","1uF","Capacitor_SMD:C_0603_1608Metric","5","",""
"C10,C11","2.2uF","Capacitor_SMD:C_0805_2012Metric","2","",""
"C13,C14","18pF","Capacitor_SMD:C_0603_1608Metric","2","",""
"C201-C205","100uF 900V film [TBV]","mcuc:MKP1848C_6pin_52.5x20.3","5","","Excluded from board"
"C311,C321,C331,C341,C351,C361","330p [TBV]","Capacitor_SMD:C_0603_1608Metric","6","",""
"C312,C314,C316,C322,C324,C326,C332,C334,C336,C342,C344,C346,C352,C354,C356,C362,C364,C366","100n","Capacitor_SMD:C_0603_1608Metric","18","",""
"C313,C315,C323,C325,C333,C335,C343,C345,C353,C355,C363,C365","1u","Capacitor_SMD:C_0805_2012Metric","12","",""
"C317,C327,C337,C347,C357,C367","100p [TBV]","Capacitor_SMD:C_0603_1608Metric","6","",""
"C502,C505,C508,C817,C819","1nF","Capacitor_SMD:C_0603_1608Metric","5","",""
"C601,C602","0.68uF 630V film [TBV]","Capacitor_SMD:C_0603_1608Metric","2","",""
"C603","10nF 1kV [TBV]","Capacitor_SMD:C_0603_1608Metric","1","",""
"C604","10uF 50V [TBV]","Capacitor_SMD:C_0603_1608Metric","1","",""
"C606","4.7uF 25V X7R [TBV]","Capacitor_SMD:C_0603_1608Metric","1","",""
"C607","100nF [TBV]","Capacitor_SMD:C_0603_1608Metric","1","",""
"C608","1nF 100V [TBV]","Capacitor_SMD:C_0603_1608Metric","1","",""
"C609,C610","220uF 25V polymer [TBV]","Capacitor_SMD:CP_Elec_8x10.5","2","",""
"C612","330pF [TBV]","Capacitor_SMD:C_0603_1608Metric","1","",""
"C613,C625","10nF [TBV]","Capacitor_SMD:C_0603_1608Metric","2","",""
"C614","2.2uF 25V X7R","Capacitor_SMD:C_0603_1608Metric","1","",""
"C620,C621","4.7uF 50V [TBV]","Capacitor_SMD:C_0805_2012Metric","2","",""
"C624","4.7uF [TBV]","Capacitor_SMD:C_0603_1608Metric","1","",""
"C626,C628","100pF [TBV]","Capacitor_SMD:C_0603_1608Metric","2","",""
"C627","47nF [TBV]","Capacitor_SMD:C_0603_1608Metric","1","",""
"C629,C630,C643,C644,C647,C648","22uF 25V [TBV]","Capacitor_SMD:C_1210_3225Metric","6","",""
"C631","1uF [TBV]","Capacitor_SMD:C_0603_1608Metric","1","",""
"C640,C645","2.2uF 50V [TBV]","Capacitor_SMD:C_0805_2012Metric","2","",""
"C650,C651,C653,C660,C666,C672,C678","10uF [TBV]","Capacitor_SMD:C_0805_2012Metric","7","",""
"C652","2.2uF [TBV]","Capacitor_SMD:C_0603_1608Metric","1","",""
"C662,C664,C668,C670,C674,C676,C680,C682","10uF 25V [TBV]","Capacitor_SMD:C_0805_2012Metric","8","",""
"C803,C805,C820","2.2uF","Capacitor_SMD:C_0603_1608Metric","3","",""
"C808,C809","15pF","Capacitor_SMD:C_0603_1608Metric","2","",""
"C810","4.7uF","Capacitor_SMD:C_0603_1608Metric","1","",""
"C811","10nF","Capacitor_SMD:C_0603_1608Metric","1","",""
"C812,C814","120pF","Capacitor_SMD:C_0603_1608Metric","2","",""
"C905","220pF","Capacitor_SMD:C_0603_1608Metric","1","",""
"C1203","4.7nF","Capacitor_SMD:C_0603_1608Metric","1","",""
"D311,D321,D331,D341,D351,D361","BAS316","Diode_SMD:D_SOD-323","6","",""
"D312,D313,D322,D323,D332,D333,D342,D343,D352,D353,D362,D363","US1M [TBV]","Diode_SMD:D_SMA","12","",""
"D401,D402","BAS316 [TBV]","Diode_SMD:D_SOD-323","2","",""
"D403","MM3Z18VT1G","Diode_SMD:D_SOD-323","1","",""
"D601","US1M-class 1kV std recovery [TBV]","Diode_SMD:D_SMA","1","",""
"D602","BAS316-class [TBV]","Diode_SMD:D_SOD-323","1","",""
"D603","SS310-class 100V 3A [TBV]","Diode_SMD:D_SMC","1","",""
"D604","SS54 [TBV]","Diode_SMD:D_SMC","1","",""
"D605,D606,D608,D609,D611,D612,D614,D615","SS310 [TBV]","Diode_SMD:D_SMC","8","",""
"D607,D610,D613,D616","BZX384-C5V1 [TBV]","Diode_SMD:D_SOD-323","4","",""
"D801-D809,D901","BAT54S","Package_TO_SOT_SMD:SOT-23","10","",""
"D902","OCP","LED_SMD:LED_0805_2012Metric","1","",""
"D903","FAULT","LED_SMD:LED_0805_2012Metric","1","",""
"D1201","NUP2105L","Package_TO_SOT_SMD:SOT-23","1","",""
"D1202","GREEN PWR","LED_SMD:LED_0805_2012Metric","1","",""
"D1203","RED FAULT","LED_SMD:LED_0805_2012Metric","1","",""
"E801","BLM21PG221SN1D","Inductor_SMD:L_0805_2012Metric","1","",""
"FB1","FerriteBead","Inductor_SMD:L_0805_2012Metric","1","",""
"J401","DC_INPUT_P tap - 6.3mm FASTON / M4 ring lug [TBV]","MountingHole:MountingHole_4.3mm_M4_Pad_Via","1","",""
"J402","to R401 chassis - 6.3mm FASTON / M4 ring lug [TBV]","MountingHole:MountingHole_4.3mm_M4_Pad_Via","1","",""
"J403","R401 return to DC_BUS_P tap - 6.3mm FASTON / M4 ring lug [TBV]","MountingHole:MountingHole_4.3mm_M4_Pad_Via","1","",""
"J404","from R424 chassis - 6.3mm FASTON / M4 ring lug [TBV]","MountingHole:MountingHole_4.3mm_M4_Pad_Via","1","",""
"J405","DC_BUS_N tap - 6.3mm FASTON / M4 ring lug [TBV]","MountingHole:MountingHole_4.3mm_M4_Pad_Via","1","",""
"J501","HOYS U harness - JST PA B05B-PASK-1 [TBV]","Connector_JST:JST_PH_B5B-PH-K_1x05_P2.00mm_Vertical","1","",""
"J502","HOYS V harness - JST PA B05B-PASK-1 [TBV]","Connector_JST:JST_PH_B5B-PH-K_1x05_P2.00mm_Vertical","1","",""
"J503","HOYS W harness - JST PA B05B-PASK-1 [TBV]","Connector_JST:JST_PH_B5B-PH-K_1x05_P2.00mm_Vertical","1","",""
"J1101","Coldplate NTC","Connector_JST:JST_PH_B2B-PH-K_1x02_P2.00mm_Vertical","1","",""
"J1201","CAN bus (H/L/GND/nc)","Connector_JST:JST_PH_B4B-PH-K_1x04_P2.00mm_Vertical","1","",""
"J1202","GCT USB4085-GF-A","Connector_USB:USB_C_Receptacle_GCT_USB4085","1","",""
"J1203","Aux 12-24 V in","Connector_JST:JST_VH_B2P-VH_1x02_P3.96mm_Vertical","1","",""
"J1204","Main contactor coil","Connector_JST:JST_VH_B4P-VH_1x04_P3.96mm_Vertical","1","",""
"J1205","Hall + motor temp","Connector_JST:JST_SH_SM08B-SRSS-TB_1x08-1MP_P1.00mm_Horizontal","1","",""
"J1206","Encoder / SinCos","Connector_JST:JST_SH_SM08B-SRSS-TB_1x08-1MP_P1.00mm_Horizontal","1","",""
"J1207","Resolver","Connector_JST:JST_SH_SM06B-SRSS-TB_1x06-1MP_P1.00mm_Horizontal","1","",""
"J1208","FTSH-105-01-L-DV-K","Connector_PinHeader_1.27mm:PinHeader_2x05_P1.27mm_Vertical_SMD","1","",""
"K401","HV DC precharge relay, >=450 V DC contacts [TBV]","mcuc:HFE80V_HTPAJ","1","",""
"L601","SRP6060FA-100M 10uH 7.6A","Inductor_SMD:L_Bourns_SRP6060FA","1","",""
"L602","SRP5030TA-4R7M 4.7uH 6A","Inductor_SMD:L_Bourns_SRP5030T","1","",""
"L603","SRR1260-120M 12uH 5A","Inductor_SMD:L_Bourns_SRR1260","1","",""
"Q311,Q321,Q331,Q341,Q351,Q361","BSS138 [TBV]","Package_TO_SOT_SMD:SOT-23","6","",""
"Q401,Q402","AO3400-class [TBV]","Package_TO_SOT_SMD:SOT-23","2","",""
"Q403","C3M0350120J [TBV]","Package_TO_SOT_SMD:TO-263-7_TabPin8","1","",""
"Q601-Q605","CSD18543Q3A-class [TBV]","Package_SON:VSON-8_3.3x3.3mm_P0.65mm_NexFET","5","",""
"R1,R803-R805,R808,R809,R811,R813,R821-R832,R909","10k","Resistor_SMD:R_0603_1608Metric","21","DNP",""
"R311,R321,R331,R341,R351,R361,R402,R404","1k [TBV]","Resistor_SMD:R_0603_1608Metric","8","",""
"R312,R322,R332,R342,R352,R362","4.87k [TBV]","Resistor_SMD:R_0603_1608Metric","6","",""
"R313,R323,R333,R343,R353,R363","1.33k [TBV]","Resistor_SMD:R_0603_1608Metric","6","",""
"R314,R324,R334,R344,R354,R364","12 [TBV]","Resistor_SMD:R_1206_3216Metric","6","",""
"R315,R325,R335,R345,R355,R365","3.3 [TBV]","Resistor_SMD:R_1206_3216Metric","6","",""
"R316,R326,R336,R346,R356,R366","1k [TBV]","Resistor_SMD:R_1206_3216Metric","6","",""
"R391,R392,R901-R908,R913,R914","4.7k","Resistor_SMD:R_0603_1608Metric","12","",""
"R393,R706,R833,R836,R1102,R1104,R1208,R1209","1k","Resistor_SMD:R_0603_1608Metric","8","",""
"R401","1.25k 50W >=41J pulse [TBV]","","1","","Excluded from board"
"R403,R405,R611","10k [TBV]","Resistor_SMD:R_0603_1608Metric","3","",""
"R411-R414","18.7k 3W [TBV]","Resistor_SMD:R_2512_6332Metric","4","",""
"R421-R424","220R 25W [TBV]","","4","","Excluded from board"
"R425","47R [TBV]","Resistor_SMD:R_0603_1608Metric","1","",""
"R426","10M","Resistor_SMD:R_0603_1608Metric","1","",""
"R427,R501,R505,R509,R911,R912","100R","Resistor_SMD:R_0603_1608Metric","6","",""
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
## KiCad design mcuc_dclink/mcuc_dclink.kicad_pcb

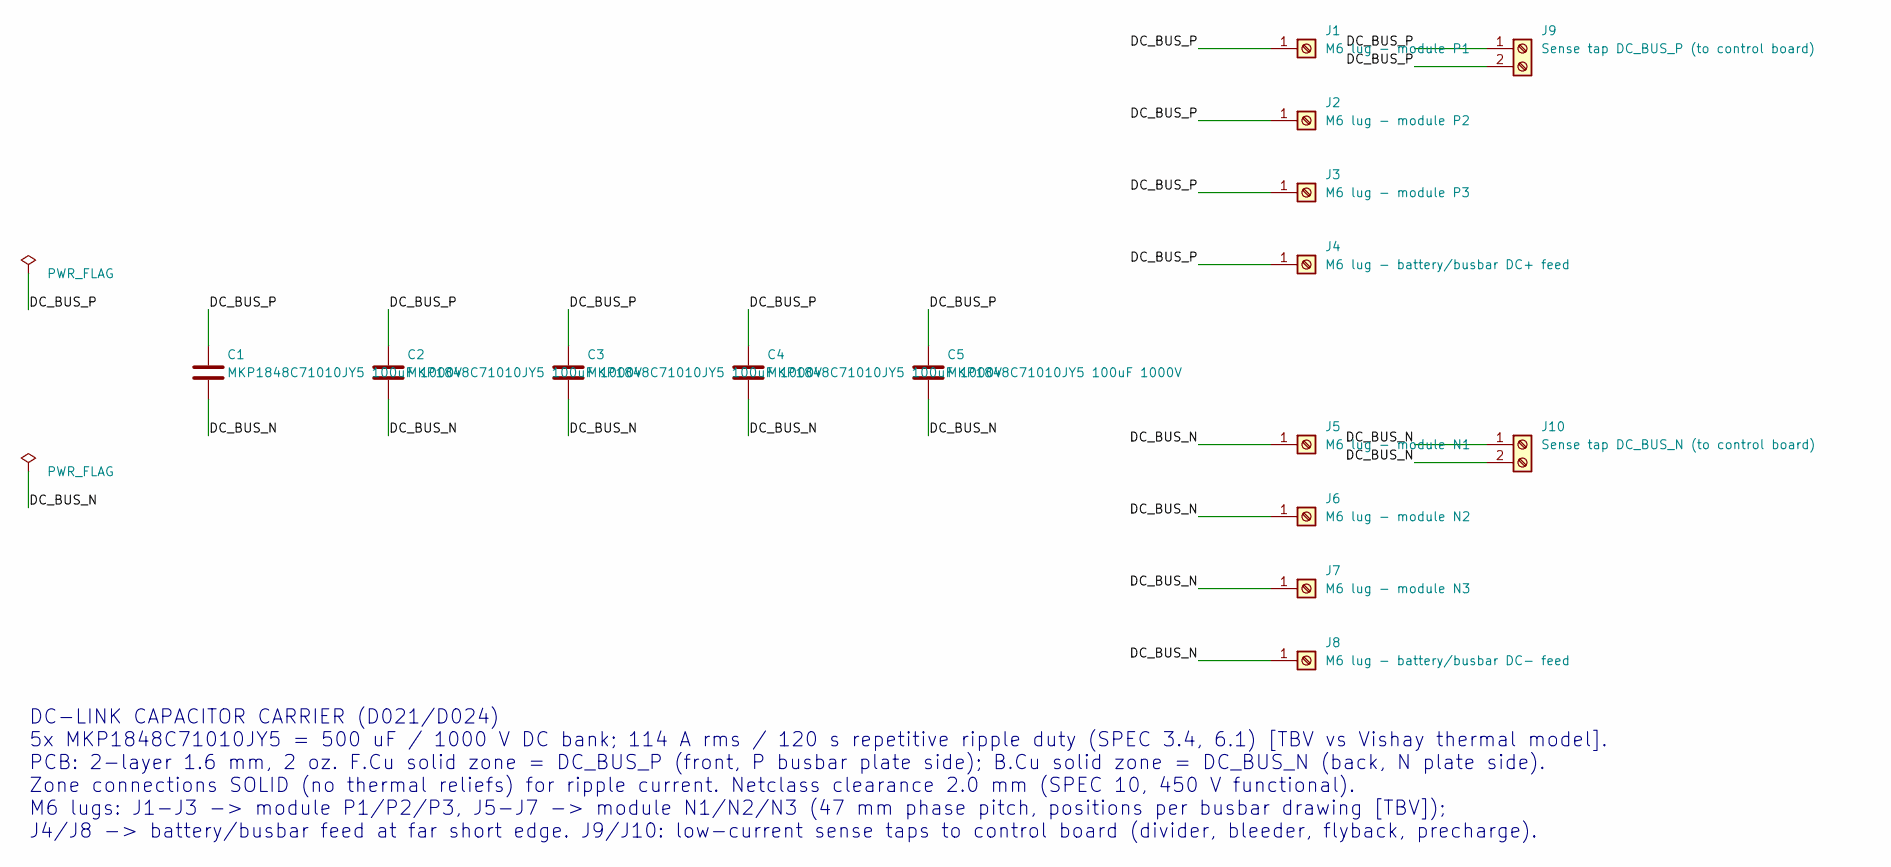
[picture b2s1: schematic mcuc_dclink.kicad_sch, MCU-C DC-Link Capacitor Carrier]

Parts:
C1, C2, C3, C4, C5: MKP1848C71010JY5 100uF 1000V; MKP1848C_6pin_52.5x20.3
J1: M6 lug - module P1; M6_LUG
J2: M6 lug - module P2; M6_LUG
J3: M6 lug - module P3; M6_LUG
J4: M6 lug - battery/busbar DC+ feed; M6_LUG
J5: M6 lug - module N1; M6_LUG
J6: M6 lug - module N2; M6_LUG
J7: M6 lug - module N3; M6_LUG
J8: M6 lug - battery/busbar DC- feed; M6_LUG
J9: Sense tap DC_BUS_P (to control board); TAP_FASTON_2xD1.5
J10: Sense tap DC_BUS_N (to control board); TAP_FASTON_2xD1.5

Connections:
/DC_BUS_N: C1.2, C2.2, C3.2, C4.2, C5.2, J5.1, J6.1, J7.1, J8.1, J10.1, J10.2
/DC_BUS_P: C1.1, C2.1, C3.1, C4.1, C5.1, J1.1, J2.1, J3.1, J4.1, J9.1, J9.2

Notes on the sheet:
DC-LINK CAPACITOR CARRIER (D021/D024) 5x MKP1848C71010JY5 = 500 uF / 1000 V DC bank; 114 A rms / 120 s repetitive ripple duty (SPEC 3.4, 6.1) [TBV vs Vishay thermal model]. PCB: 2-layer 1.6 mm, 2 oz. F.Cu solid zone = DC_BUS_P (front, P busbar plate side); B.Cu solid zone = DC_BUS_N (back, N plate 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

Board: 2 copper layers, 22 parts (4 on the bottom side), 2 nets, no tracks yet.

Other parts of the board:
FID1, FID2, FID3: Fiducial; Fiducial_1mm_Mask2mm
H1, H2, H3, H4: M4 mounting hole; MountingHole_4.3mm_M4

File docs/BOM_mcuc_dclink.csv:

"Reference","Value","Footprint","QUANTITY"
"C1-C5","MKP1848C71010JY5 100uF 1000V","mcuc:MKP1848C_6pin_52.5x20.3","5"
"J1","M6 lug - module P1","mcuc_dclink:M6_LUG","1"
"J2","M6 lug - module P2","mcuc_dclink:M6_LUG","1"
"J3","M6 lug - module P3","mcuc_dclink:M6_LUG","1"
"J4","M6 lug - battery/busbar DC+ feed","mcuc_dclink:M6_LUG","1"
"J5","M6 lug - module N1","mcuc_dclink:M6_LUG","1"
"J6","M6 lug - module N2","mcuc_dclink:M6_LUG","1"
"J7","M6 lug - module N3","mcuc_dclink:M6_LUG","1"
"J8","M6 lug - battery/busbar DC- feed","mcuc_dclink:M6_LUG","1"
"J9","Sense tap DC_BUS_P (to control board)","mcuc_dclink:TAP_FASTON_2xD1.5","1"
"J10","Sense tap DC_BUS_N (to control board)","mcuc_dclink:TAP_FASTON_2xD1.5","1"
